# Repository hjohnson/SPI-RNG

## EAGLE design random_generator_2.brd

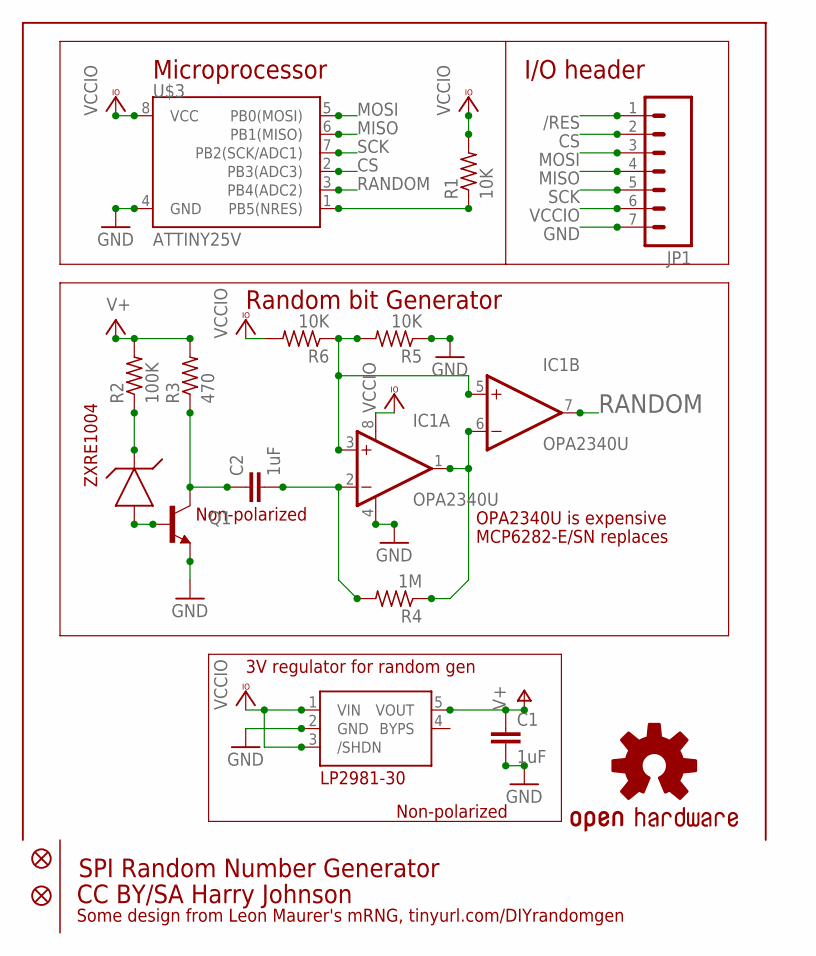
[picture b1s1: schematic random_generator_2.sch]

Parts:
C1, C2: 1uF; 0805
IC1: OPA2340U; SO08
JP1: M07; 1X07
JP2, JP3: FIDUCIALUFIDUCIAL; MICRO-FIDUCIAL
Q1: TRANSISTOR_NPNSOT23; SOT23
R1, R5, R6: 10K; R0805
R2: 100K; R0805
R3: 470; R0805
R4: 1M; R0805
U$1: ZXRE1004FFTA; SOT23
U$2: TC1014; SOT23-5L
U$3: ATTINY25V; SO08-EIAJ
U$4: OSHW-LOGOS; OSHW-LOGO-S

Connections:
/RES: JP1.1, R1.1, U$3.1 (PB5(NRES))
CS: JP1.2, U$3.2 (PB3(ADC3))
GND: C1.2, IC1.4 (V-), JP1.7, Q1.2 (E), R5.1, U$2.2 (GND), U$3.4 (GND)
MISO: JP1.4, U$3.6 (PB1(MISO))
MOSI: JP1.3, U$3.5 (PB0(MOSI))
unnamed: Q1.1 (B), U$1.2 (A)
unnamed: C2.1, Q1.3 (C), R3.1
unnamed: R2.1, U$1.1 (K)
unnamed: C2.2, IC1.2 (-IN), R4.2
unnamed: IC1.1 (OUT), IC1.6 (-IN), R4.1
unnamed: IC1.3 (+IN), IC1.5 (+IN), R5.2, R6.1
RANDOM: IC1.7 (OUT), U$3.3 (PB4(ADC2))
SCK: JP1.5, U$3.7 (PB2(SCK/ADC1))
V+: C1.1, R2.2, R3.2, U$2.5 (VOUT)
VCCIO: IC1.8 (V+), JP1.6, R1.2, R6.2, U$2.1 (VIN), U$2.3 (/SHDN), U$3.8 (VCC)

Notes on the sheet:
Random bit Generator
ZXRE1004
3V regulator for random gen
Microprocessor
I/O header
SPI Random Number Generator
CC BY/SA Harry Johnson
Some design from Leon Maurer's mRNG, tinyurl.com/DIYrandomgen
LP2981-30
OPA2340U is expensive
MCP6282-E/SN replaces
Non-polarized

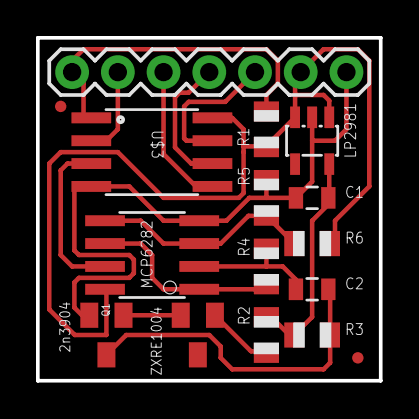
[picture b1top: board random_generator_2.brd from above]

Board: 2 copper layers, 19.1 x 19.1 mm, 17 parts (1 on the bottom side), 15 nets.

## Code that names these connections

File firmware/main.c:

/* Name: main.c
 * Author: Harry Johnson
 * License: CC BY/SA unported.
 * SPI interfaced True Hardware Random Number Generator: Keep shifting in bytes, and it will keep shifting random bytes out. 
 * This is an SPI slave, and technically doesn't need to recieve data, but the MOSI line is included for future use. (There is spare memory space..) 
 * Setup in the main routine, everything else is handled in ISRs. One ISR updates the random value, and another ISR handles SPI communication.
 *
 * PINOUT:
 * PB0: MOSI
 * PB1: MISO
 * PB2: SCK
 * PB3: CS/SS (Slave Select)
 * PB4: Input from RNG hardware.
 * PB5: /RESET
 */

#include <avr/io.h> //Device-specific IO pins.
#include <avr/interrupt.h> //Interrupts
#include <stdint.h> //standard int types.

#define mixInBit(bit)	randomNumber = (randomNumber >> 1) | (((bit ^ (randomNumber >> 0) ^ (randomNumber >> 3)) & 1) << 24) //Feedback Shift Register to mix in a new bit to the number.

volatile unsigned long randomNumber = 0b1010101010101010101010101; //32 bit random number, always being refreshed.
volatile unsigned char lastbit = 255; //what the last input digit was, or 255 if we want to force a start-over. (after outputting a bit)

int main(void)
{
    WDTCR |= (1<<WDCE) | (WDE); 
    WDTCR &= ~(1<<WDE); //disable the watchdog timers.

    ADCSRA = 0; //disable the ADC, just in case.
    PRR |= (1<<PRADC) | (1<<PRTIM0); //power down the ADC and timer0.
    ACSR |= ~(1<<ACIE); 
    ACSR |= (1<<ACD); //disable the analog comparator.
    
    cli(); //disable interrupts for the meantime.
    DDRB = (1<<1); //PB1 is MISO pin, everything else is inputs.
    PORTB |= (1<<3); //enable CS pin internal pullup.
    PCMSK = (1<<PCINT3); //pin change interrupt 3 enabled, everything else disabled. (CS pin only)
    GIMSK |= (1<<PCIE); //pin change interrupts enabled in general.
    
    TIMSK = (1<<OCIE1A); //enable output compare match interrupt.
    OCR1A = 0x40; //trigger every 8Mhz/128 = 62500 Hz, oversampling noise, which is around 20Khz or so. 
    GTCCR = 0; //no PWM or anything of the sort.
    TCCR1 = (1<<CS10);// | (1<<CS10); //reset counter 1, and set clock source to System Clock (8Mhz).
    
    USICR = (1<<USIWM0) | (1<<USICS1); //Enable SPI, and select the Clock pin to be the clock source.
    sei(); //re-enable interrupts.
    for(;;){
    }
    return 0;   /* never reached */
}

//USI (SPI) overflow vector: Every 8 bits, this triggers.
//if the value sent from the master is from 1-2, then make that the number of bytes of random number to send. 
//if it isn't, and there is a byte to send, send it, and decrement the byte send counter.
ISR(USI_OVF_vect) { 
    USIDR = randomNumber & 0xFF; //return the lowest byte of the current number. Result will be decimal integer, 0-255.
    USISR |= (1<<USIOIF); //clear overflow register.
}

ISR(PCINT0_vect) { //pin change vector: only CS pin is enabled, so this must be a transition on CS.
    if((PINB & (1<<3))==1) { //CS is high, disable SPI.
        DDRB &= ~(1<<1); //MISO pin disable.
        USICR &= ~(1<<USIOIE); //disable the SPI overflow vector.
    } else { //else CS is low. Time to get into SPI mode!
        DDRB |= (1<<1); //MISO pin re-enable
        USISR &= 0xF0; //reset the clock.
        USISR |= (1<<USIOIF); //clear overflow interrupt flag, just in case.
        USICR |= (1<<USIOIE); //enable the overflow interrupt.  
}
    
}

ISR(TIM1_COMPA_vect) {  //triggers on a 62500KHz clock. ((8MHz/128): 1 for prescaler, 128 for counter. random input on PB4.
    TCNT1=0; //reset the counter
    if((lastbit != (PINB&(1<<4))) && (lastbit != 255)) { //if there are 2 bits, and they aren't equal. (Von Neumann)
        mixInBit(lastbit); // update the number.
        lastbit = 255; //and start the sequence of capturing another 2 bits.
    } else {
        lastbit = (PINB&(1<<4)); //capture the first bit.
    }
}

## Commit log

2012-03-04 SPI RNG: SPI accessible RNG board.
    Small (.75" x .75") Random Number Generator, accessible via SPI. Would
    I trust it for crypto? No, not really, not yet. Is it still cool? Yes,
    I believe so. OSHW: Schematic, board, firmware, and BOM/quote files.
2012-03-25 Added end files (hex, etc).
2012-03-25 removed DS Store (apple files)
2012-04-17 MANY BUGS! NOW, HANDLE IT!
    A whole nightmarish mess of bugs fixed: Dr Nyquist prescribed some
    faster sampling, (just in case). I also tied op amp to VCCIO instead of
    3V (for voltage swings guaranteed to trigger logic high), SPI/USI code
    now works too. WIll upload an Arduino test program soon…
2012-04-17 Updates to BOM/Quote, and slight update to board: tweaked everything around a bit to give easier PnP placement
2012-04-18 Added a subdirectory: random_read. This is an Arduino program I used to test the RNG, as well as an example of its results (200K random numbers) and a histogram of said results.
2012-04-18 Revert "Added a subdirectory: random_read. This is an Arduino program I used to test the RNG, as well as an example of its results (200K random numbers) and a histogram of said results."
    This reverts commit 813bcb698b103c1f062770043ea5ba36d0701cd2.
2012-04-18 Revert "Revert "Added a subdirectory: random_read. This is an Arduino program I used to test the RNG, as well as an example of its results (200K random numbers) and a histogram of said results.""
    This reverts commit e8bffbb2eab26593f465c9e83c66a3b4be4fae53.
2012-04-18 Removed .DS_Store
2012-04-19 Added/fixed comments in firmware, made component designators a bit bigger.
2012-04-22 Bumped up the delay on random_read.ino a bit and increased firmware sampling speed on the von neumann routine to cover my bases a bit more. As of now, 250Kbytes of binary passes a good number of the 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

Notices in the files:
random_generator_2.brd:
CC BY/SA HMJ
parts and their libraries:
SparkFun: Licensing: CC v3.0 Share-Alike You are welcome to use this library for commercial purposes.
